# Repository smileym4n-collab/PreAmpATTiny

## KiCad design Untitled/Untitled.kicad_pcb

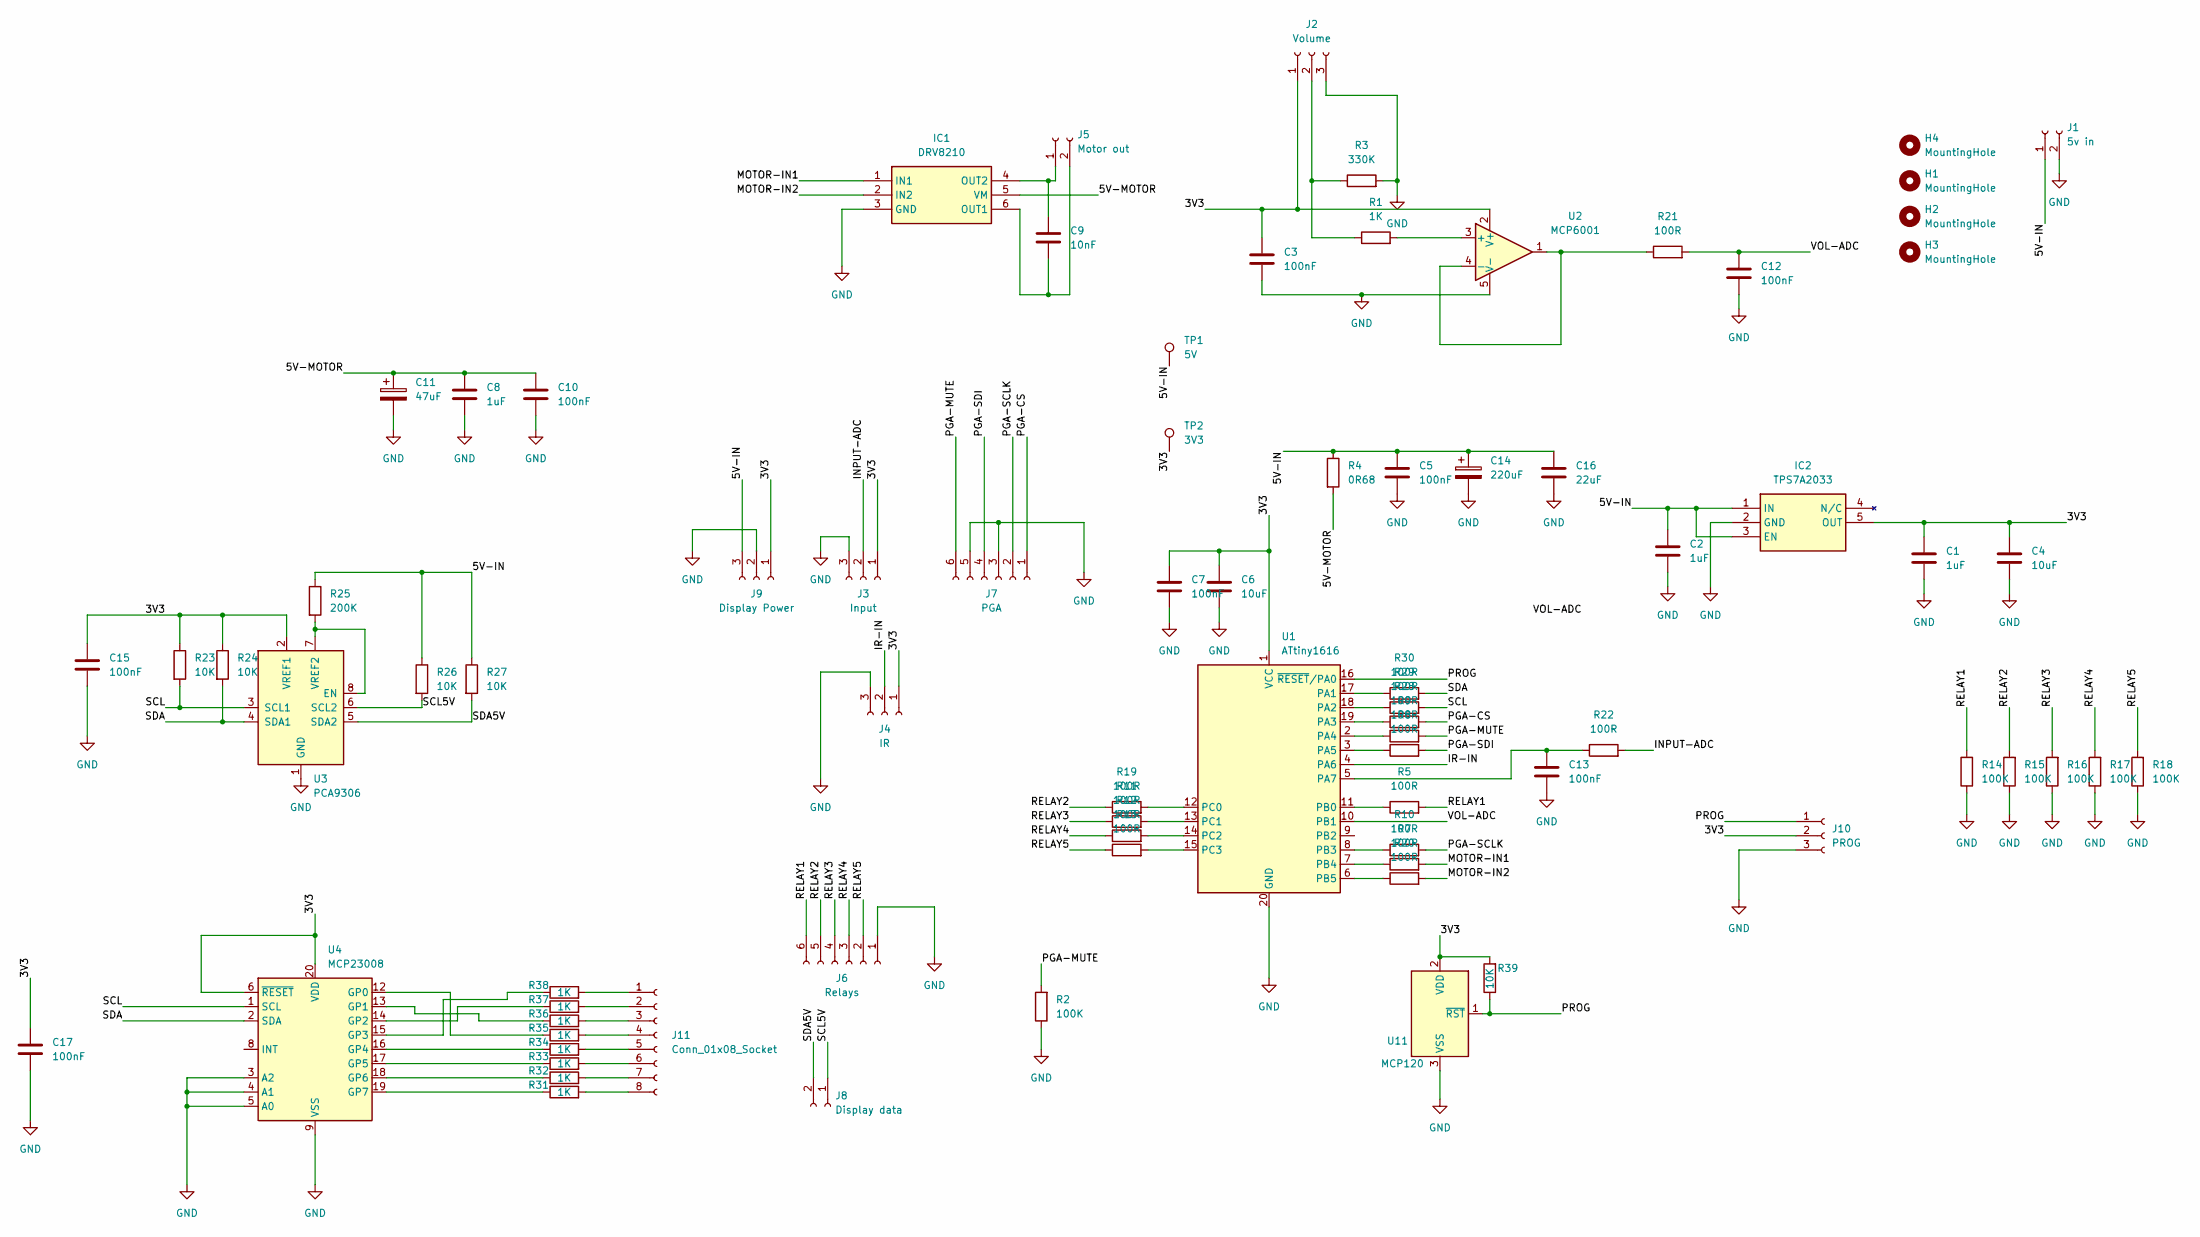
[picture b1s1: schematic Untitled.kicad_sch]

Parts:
C1, C2, C8: 1uF; C_1206_3216Metric_Pad1.33x1.80mm_HandSolder
C3, C5, C7, C10, C12, C13, C15, C17: 100nF; C_1206_3216Metric_Pad1.33x1.80mm_HandSolder
C4, C6: 10uF; C_1206_3216Metric_Pad1.33x1.80mm_HandSolder
C9: 10nF; C_0805_2012Metric_Pad1.18x1.45mm_HandSolder
C11: 47uF; CP_Radial_D6.3mm_P2.50mm
C14: 220uF; CP_Radial_D6.3mm_P2.50mm
C16: 22uF; C_1206_3216Metric_Pad1.33x1.80mm_HandSolder
H1, H2, H3, H4: MountingHole; MountingHole_4mm
IC1: DRV8210; Mouser Part Number 595-DRV8210DRLR
IC2: TPS7A2033; SOT95P280X145-5N; Mouser Part Number 595-TPS7A2033PDBVR
J1: 5v in; JST_XH_B2B-XH-A_1x02_P2.50mm_Vertical
J2: Volume; JST_XH_B3B-XH-A_1x03_P2.50mm_Vertical
J3: Input; JST_XH_B3B-XH-A_1x03_P2.50mm_Vertical
J4: IR; JST_XH_B3B-XH-A_1x03_P2.50mm_Vertical
J5: Motor out; JST_XA_B02B-XASK-1_1x02_P2.50mm_Vertical
J6: Relays; JST_XH_B6B-XH-A_1x06_P2.50mm_Vertical
J7: PGA; JST_XH_B6B-XH-A_1x06_P2.50mm_Vertical
J8: Display data; JST_XA_B02B-XASK-1_1x02_P2.50mm_Vertical
J9: Display Power; JST_XH_B3B-XH-A_1x03_P2.50mm_Vertical
J10: PROG; PinSocket_1x03_P2.54mm_Vertical
J11: Conn_01x08_Socket; PinHeader_1x08_P2.54mm_Vertical
R1, R31, R32, R33, R34, R35, R36, R37, R38: 1K; R_0805_2012Metric_Pad1.20x1.40mm_HandSolder
R2, R14, R15, R16, R17, R18: 100K; R_0805_2012Metric_Pad1.20x1.40mm_HandSolder
R3: 330K; R_0805_2012Metric_Pad1.20x1.40mm_HandSolder
R4: 0R68; R_1206_3216Metric_Pad1.30x1.75mm_HandSolder
R5, R7, R8, R9, R10, R11, R12, R13, R19, R20, R21, R22, R28, R29, R30: 100R; R_0805_2012Metric_Pad1.20x1.40mm_HandSolder
R23, R24, R26, R27: 10K; R_0603_1608Metric_Pad0.98x0.95mm_HandSolder
R25: 200K; R_0603_1608Metric_Pad0.98x0.95mm_HandSolder
R39: 10K; R_0805_2012Metric_Pad1.20x1.40mm_HandSolder
TP1: 5V; TestPoint_Pad_2.0x2.0mm
TP2: 3V3; TestPoint_Pad_2.0x2.0mm
U1: ATtiny1616; SSOP-20_5.3x7.2mm_P0.65mm
U2: MCP6001; SOT-23-5
U3: PCA9306; SSOP-8_2.95x2.8mm_P0.65mm
U4: MCP23008; SSOP-20_5.3x7.2mm_P0.65mm
U11: MCP120; SOT-23

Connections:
/3V3: C1.1, C3.1, C4.1, C6.1, C7.1, C15.1, C17.1, IC2.5 (OUT), J2.1, J3.1, J4.1, J9.1, J10.2, R23.1, R24.1, R39.2, TP2.1, U1.1 (VCC), U2.2 (V+), U3.2 (VREF1), U4.6 (~RESET), U4.20 (VDD), U11.2 (VDD)
/5V-IN: C2.1, C5.1, C14.1, C16.1, IC2.1 (IN), IC2.3 (EN), J1.1, J9.3, R4.1, R25.1, R26.1, R27.1, TP1.1
/5V-MOTOR: C8.1, C10.1, C11.1, IC1.5 (VM), R4.2
/INPUT-ADC: J3.2, R22.2
/IR-IN: J4.2, U1.4 (PA6)
/MOTOR-IN1: IC1.1 (IN1), R7.2
/MOTOR-IN2: IC1.2 (IN2), R20.2
/PGA-CS: J7.1, R28.2
/PGA-MUTE: J7.6, R2.2, R9.2
/PGA-SCLK: J7.2, R10.2
/PGA-SDI: J7.4, R8.2
/PROG: J10.1, R39.1, U1.16 (~RESET/PA0), U11.1 (~RST)
/RELAY1: J6.6, R5.2, R14.2
/RELAY2: J6.5, R15.2, R19.1
/RELAY3: J6.4, R11.1, R16.2
/RELAY4: J6.3, R12.1, R17.2
/RELAY5: J6.2, R13.1, R18.2
/SCL: R23.2, R29.2, U3.3 (SCL1), U4.1 (SCL)
/SCL5V: J8.1, R26.2, U3.6 (SCL2)
/SDA: R24.2, R30.2, U3.4 (SDA1), U4.2 (SDA)
/SDA5V: J8.2, R27.2, U3.5 (SDA2)
/VOL-ADC: C12.1, R21.2, U1.10 (PB1)
GND: C1.2, C2.2, C3.2, C4.2, C5.2, C6.2, C7.2, C8.2, C10.2, C11.2, C12.2, C13.2, C14.2, C15.2, C16.2, C17.2, IC1.3 (GND), IC2.2 (GND), J1.2, J2.3, J3.3, J4.3, J6.1, J7.3, J7.5, J9.2, J10.3, R2.1, R3.2, R14.1, R15.1, R16.1, R17.1, R18.1, U1.20 (GND), U2.5 (V-), U3.1 (GND), U4.3 (A2), U4.4 (A1), U4.5 (A0), U4.9 (VSS), U11.3 (VSS)
unnamed: C9.2, IC1.6 (OUT1), J5.2
unnamed: C9.1, IC1.4 (OUT2), J5.1
unnamed: J2.2, R1.1, R3.1
unnamed: J11.1, R38.2
unnamed: J11.2, R37.2
unnamed: J11.3, R36.2
unnamed: J11.4, R35.2
unnamed: J11.5, R34.2
unnamed: J11.6, R33.2
unnamed: J11.7, R32.2
unnamed: J11.8, R31.2
unnamed: R30.1, U1.17 (PA1)
unnamed: R29.1, U1.18 (PA2)
unnamed: R28.1, U1.19 (PA3)
unnamed: R9.1, U1.2 (PA4)
unnamed: R8.1, U1.3 (PA5)
unnamed: C13.1, R22.1, U1.5 (PA7)
unnamed: R5.1, U1.11 (PB0)
unnamed: R10.1, U1.8 (PB3)
unnamed: R7.1, U1.7 (PB4)
unnamed: R20.1, U1.6 (PB5)
unnamed: R19.2, U1.12 (PC0)
unnamed: R11.2, U1.13 (PC1)
unnamed: R12.2, U1.14 (PC2)
unnamed: R13.2, U1.15 (PC3)
unnamed: R1.2, U2.3 (+)
unnamed: R21.1, U2.1, U2.4 (-)
unnamed: R25.2, U3.7 (VREF2), U3.8 (EN)
unnamed: R35.1, U4.12 (GP0)
unnamed: R36.1, U4.13 (GP1)
unnamed: R37.1, U4.14 (GP2)
unnamed: R38.1, U4.15 (GP3)
unnamed: R34.1, U4.16 (GP4)
unnamed: R33.1, U4.17 (GP5)
unnamed: R32.1, U4.18 (GP6)
unnamed: R31.1, U4.19 (GP7)

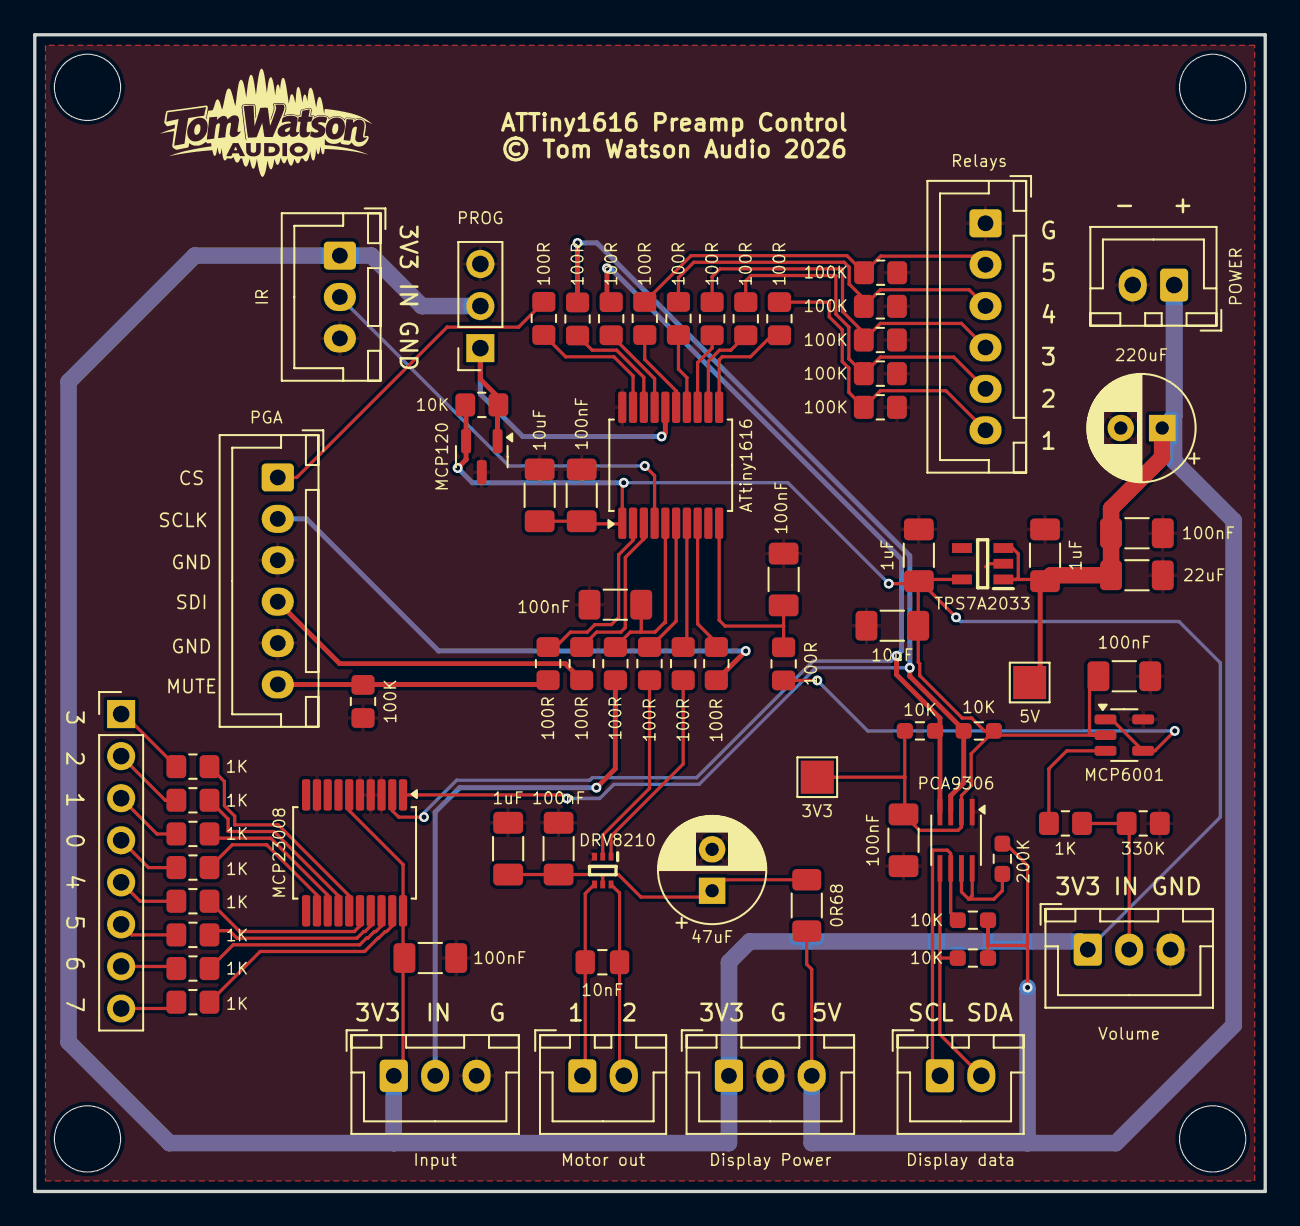
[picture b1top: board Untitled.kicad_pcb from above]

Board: 2 copper layers, 74.3 x 69.9 mm, 79 parts (0 on the bottom side), 59 nets.

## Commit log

2026-06-02 added I2C expander
2026-06-02 MCP120-300 additiob

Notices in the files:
Untitled/Untitled.kicad_pcb:
© Tom Watson Audio 2026
